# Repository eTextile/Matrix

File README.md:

# E256 - eTextile matrix sensor
### Transforming textiles into an intuitive way to interact with computers
This project is still in a beta phase, where drastic changes may occur and backwards compatibility is not guaranteed until the final release.

## About The project
Using a fabric to sense the touch is now possible with the E256 - eTextile matrix sensor.
The E256 development kit is a highly customizable solution for designers, makers, and companies who want to combine textile and programming into new eTextile projects.
This kit features 30cm by 30cm sensitive textile that allows multi-touch sensing and pressures topographic analysis.
Made out of conductive textile shaped in rows and columns and a layer of piezoresistive fabric, this textile sensor is designed to be easy to make.
The E256 firmware implements all the functionalities to sense the touch and trigger OSC messages that can be used in many application such as PureData, SuperCollider, etc.
The E256 firmware is running on Teensy 3.1 & 3.2 MCUs.
The electronic hardware and the firmware are free and open source and can be easily ported to others Arduino like microcontrollers.
In order to use the sensor in combination with any mobile devices, the E256 firmware will be ported on MCU with BLE capabilities.
From the beginning, this project stimulates the development of technologies in artistic use cases: playing music, combine graphics and sound, imagine objects that can have tactile properties, etc.

### Development tools & DOCs
* **Web page:** [http://matrix.eTextile.org/](http://matrix.eTextile.org "Web page")
* **Repository:** [https://github.com/eTextile/Matrix/tree/master](https://github.com/eTextile/Matrix/tree/master "Project repository")
* **License:** [CC-BY-SA](https://github.com/eTextile/Matrix/tree/Blob/LICENSE "E256 Matrix license")
* **Mail:** [matrix@etextile.org](mailto:contact@etextile.org "eMail")
* **Pictures:** [flickr.com](https://www.flickr.com/photos/maurin/albums/72157673740361510/ "Share your pictures with us")

## Project content
* **Hardware_textile:** eTextile matrix sensor tutorial
* **Hardware_electronic:** extension board PCB sources
* **Firmware:** embedded blob detection with OSC communication
* **Softwear:** demos made with cool applications

## Publications
- [NIME17](http://www.nime2017.org/) - Designing a Multi-Touch eTextile for Music Performances / [Paper](https://github.com/eTextile/Matrix/blob/teensy_matrix/docs/publications/NIME17-eTextile.pdf) - [Video](https://vimeo.com/217690743)
- [MOCO17](http://moco17.movementcomputing.org/) - Music Skin: Fabric Interface for Expressive Music Control / [Paper](https://github.com/eTextile/Matrix/blob/teensy_matrix/docs/publications/MOCO17-MusicSkin.pdf)

## Copyright
Except as otherwise noted, all files in the **E256 eTextile-matrix-sensor** project folder

    Copyright (c) 2014-2020 Maurin Donneaud

For information on usage and redistribution, and for a DISCLAIMER OF ALL
WARRANTIES, see LICENSE.txt included in the resistiveMatrix project folder.

## Acknowledgements
Thanks to Vincent Roudaut, Hannah Perner Willson, Cedric Honnet, Antoine Meisso, Paul Strohmeier

## Docs
- [Video made at Schmiede 2014](http://www.kobakant.at/DIY/?p=4305/)

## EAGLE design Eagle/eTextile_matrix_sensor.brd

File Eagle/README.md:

# e-Textile matrix sensor

- Purpose : 16x16 e-textile matrix sensors
- Copyright (c) 2014 Maurin Donneaud
- Licence : GNU GENERAL PUBLIC LICENSE
- Web site : http://etextile.org

## Partslist

| Part        |    Value                     |     Device              |          Package     |
|-------------|:-----------------------------|:------------------------|:---------------------|
ANALOG_INPUT  | 3.3V                         | PINHD-1X16/90           | 1X16/90              |
ANALOG_INPUT1 | 3.3V                         | PINHD-1X16              | 1X16                 |
C1            | 4.7uF                        | CAP0805                 | 0805                 |
C2            | 4.7uF                        | CAP0805                 | 0805                 |
C3            | 10uf                         | CPOL-EUE1.8-4           | E1,8-4               |
D1            | RED                          | LED1206                 | LED-1206             |
D11           | RED                          | LED1206                 | LED-1206             |
DIGITAL_OUT   |                              | PINHD-1X16/90           | 1X16/90              |
DIGITAL_OUT1  | 3.3V                         | PINHD-1X16/90           | 1X16/90              |
JP7           | LiPo Battery                 | M02-JST-2MM-SMT         | JST-2-SMD            |
R1            | 2K                           | RESISTOR0805-RES        | 0805                 |
R2            | 330                          | RESISTOR0805-RES        | 0805                 |
R3            | 330                          | RESISTOR0805-RES        | 0805                 |
RN1           | 3.3V                         | G08R                    | SIL9                 |
RN2           | 3.3V                         | G08R                    | SIL9                 |
S1            | SWITCH                       | SWITCH-SPSTSMD          | AYZ0202              |
SWITCH1       | SWITCH-MOMENTARY-2           | SWITCH-MOMENTARY-2      | TACTILE_SWITCH_TALL  |
U$1           | TEENSY_3.1_ALL_PINS_AND_PADS | TEENSY_3.1_ALL_PINS_AND_PADS | TEENSY_3.1_ALLPINS   |
U1            | MCP73831                     | MCP73831                     | SOT23-5              |
U3            |                              | AUDIO-JACKSMD2               | AUDIO-JACK-3.5MM-SMD |

## TODO
- Replace the Teensy With an other chip
  - keep compatibility with the Teensy audo lib : http://www.pjrc.com/teensy/td_libs_Audio.html
- Make the design with Upverter

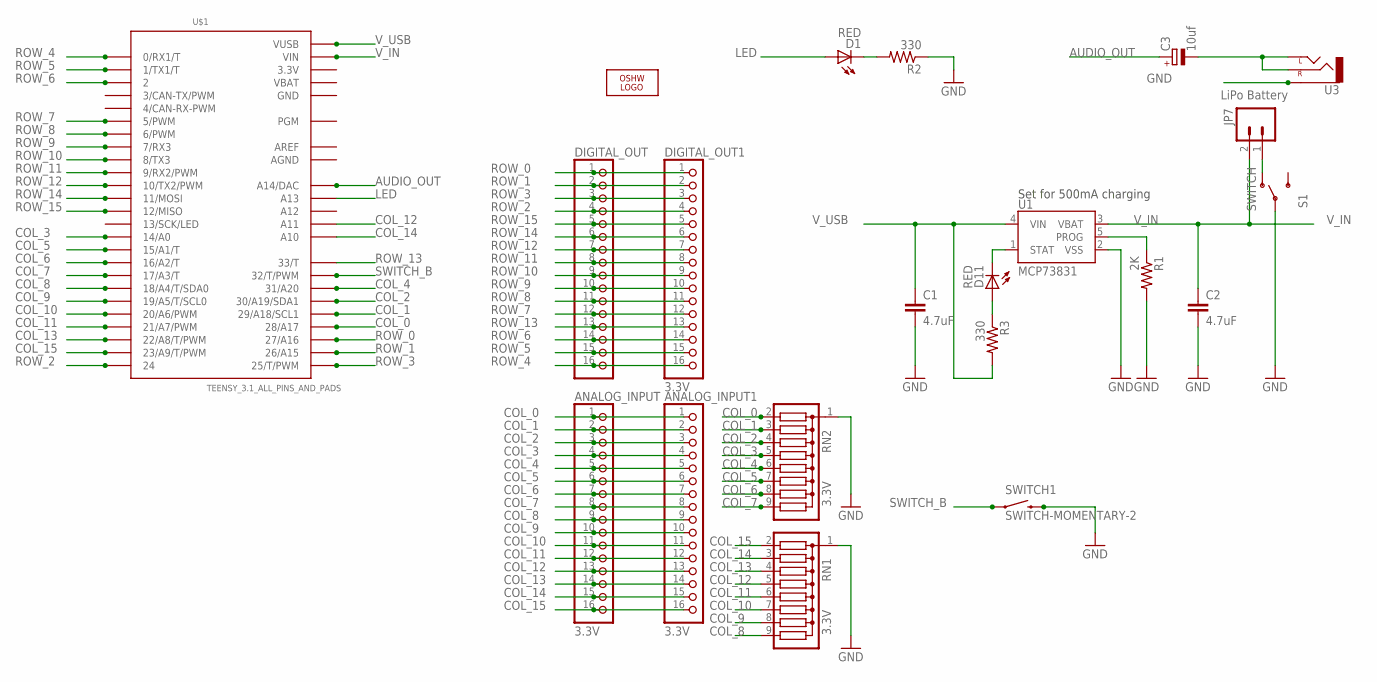
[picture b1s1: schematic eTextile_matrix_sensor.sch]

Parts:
ANALOG_INPUT: 3.3V; 1X16/90
ANALOG_INPUT1: 3.3V; 1X16
C1, C2: 4.7uF; 0805
C3: 10uf; E1,8-4
D1, D11: RED; LED-1206
DIGITAL_OUT: PINHD-1X16/90; 1X16/90
DIGITAL_OUT1: 3.3V; 1X16/90
JP7: LiPo Battery; JST-2-SMD
LOGO1: OSHW_LOGO_8MILX0350-NT; OSHW_8X350_NOTEXT
R1: 2K; 0805
R2, R3: 330; 0805
RN1, RN2: 3.3V; SIL9
S1: SWITCH; AYZ0202
SWITCH1: SWITCH-MOMENTARY-2; TACTILE_SWITCH_TALL
U1: MCP73831; SOT23-5
U3: AUDIO-JACKSMD2; AUDIO-JACK-3.5MM-SMD
U$1: TEENSY_3.1_ALL_PINS_AND_PADS; TEENSY_3.1_ALLPINS

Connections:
3.3V: U$1.3.3V, U$1.3.3V1 (3.3V), U$1.3.3V2 (3.3V)
AGND: U$1.AGND
AREF: U$1.AREF
AUDIO_OUT: C3.+, U$1.A14 (A14/DAC)
COL_0: ANALOG_INPUT.1, ANALOG_INPUT1.1, RN2.2, U$1.28 (28/A17)
COL_1: ANALOG_INPUT.2, ANALOG_INPUT1.2, RN2.3, U$1.29 (29/A18/SCL1)
COL_2: ANALOG_INPUT.3, ANALOG_INPUT1.3, RN2.4, U$1.30 (30/A19/SDA1)
COL_3: ANALOG_INPUT.4, ANALOG_INPUT1.4, RN2.5, U$1.14/A0
COL_4: ANALOG_INPUT.5, ANALOG_INPUT1.5, RN2.6, U$1.31 (31/A20)
COL_5: ANALOG_INPUT.6, ANALOG_INPUT1.6, RN2.7, U$1.15/A1 (15/A1/T)
COL_6: ANALOG_INPUT.7, ANALOG_INPUT1.7, RN2.8, U$1.16/A2 (16/A2/T)
COL_7: ANALOG_INPUT.8, ANALOG_INPUT1.8, RN2.9, U$1.17/A3 (17/A3/T)
COL_8: ANALOG_INPUT.9, ANALOG_INPUT1.9, RN1.9, U$1.18/A4 (18/A4/T/SDA0)
COL_9: ANALOG_INPUT.10, ANALOG_INPUT1.10, RN1.8, U$1.19/A5 (19/A5/T/SCL0)
COL_10: ANALOG_INPUT.11, ANALOG_INPUT1.11, RN1.7, U$1.20/A6 (20/A6/PWM)
COL_11: ANALOG_INPUT.12, ANALOG_INPUT1.12, RN1.6, U$1.21/A7 (21/A7/PWM)
COL_12: ANALOG_INPUT.13, ANALOG_INPUT1.13, RN1.5, U$1.A11
COL_13: ANALOG_INPUT.14, ANALOG_INPUT1.14, RN1.4, U$1.22/A8 (22/A8/T/PWM)
COL_14: ANALOG_INPUT.15, ANALOG_INPUT1.15, RN1.3, U$1.A10
COL_15: ANALOG_INPUT.16, ANALOG_INPUT1.16, RN1.2, U$1.23/A9 (23/A9/T/PWM)
GND: C1.2, C2.2, R1.2, R2.1, RN1.1, RN2.1, S1.2, SWITCH1.B2 (2), U1.2 (VSS), U3.SLEEVE, U$1.GND, U$1.GND1 (GND), U$1.GND2 (GND)
LED: D1.A, U$1.A13
unnamed: C3.-, U3.RING (RIGHT), U3.TIP (LEFT)
unnamed: D11.A, R3.1
unnamed: JP7.1, S1.1 (O)
unnamed: D1.C, R2.2
PROG: R1.1, U1.5 (PROG)
ROW_0: DIGITAL_OUT.1, DIGITAL_OUT1.1, U$1.27 (27/A16)
ROW_1: DIGITAL_OUT.2, DIGITAL_OUT1.2, U$1.26 (26/A15)
ROW_2: DIGITAL_OUT.4, DIGITAL_OUT1.4, U$1.24
ROW_3: DIGITAL_OUT.3, DIGITAL_OUT1.3, U$1.25 (25/T/PWM)
ROW_4: DIGITAL_OUT.16, DIGITAL_OUT1.16, U$1.0 (0/RX1/T)
ROW_5: DIGITAL_OUT.15, DIGITAL_OUT1.15, U$1.1 (1/TX1/T)
ROW_6: DIGITAL_OUT.14, DIGITAL_OUT1.14, U$1.2
ROW_7: DIGITAL_OUT.12, DIGITAL_OUT1.12, U$1.5 (5/PWM)
ROW_8: DIGITAL_OUT.11, DIGITAL_OUT1.11, U$1.6 (6/PWM)
ROW_9: DIGITAL_OUT.10, DIGITAL_OUT1.10, U$1.7 (7/RX3)
ROW_10: DIGITAL_OUT.9, DIGITAL_OUT1.9, U$1.8 (8/TX3)
ROW_11: DIGITAL_OUT.8, DIGITAL_OUT1.8, U$1.9 (9/RX2/PWM)
ROW_12: DIGITAL_OUT.7, DIGITAL_OUT1.7, U$1.10 (10/TX2/PWM)
ROW_13: DIGITAL_OUT.13, DIGITAL_OUT1.13, U$1.33 (33/T)
ROW_14: DIGITAL_OUT.6, DIGITAL_OUT1.6, U$1.11 (11/MOSI)
ROW_15: DIGITAL_OUT.5, DIGITAL_OUT1.5, U$1.12 (12/MISO)
STAT: D11.C, U1.1 (STAT)
SWITCH_B: SWITCH1.A2 (1), U$1.32 (32/T/PWM)
VBAT: U$1.VBAT
V_IN: C2.1, JP7.2, U1.3 (VBAT), U$1.VIN
V_USB: C1.1, R3.2, U1.4 (VIN), U$1.VUSB

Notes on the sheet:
Set for 500mA charging

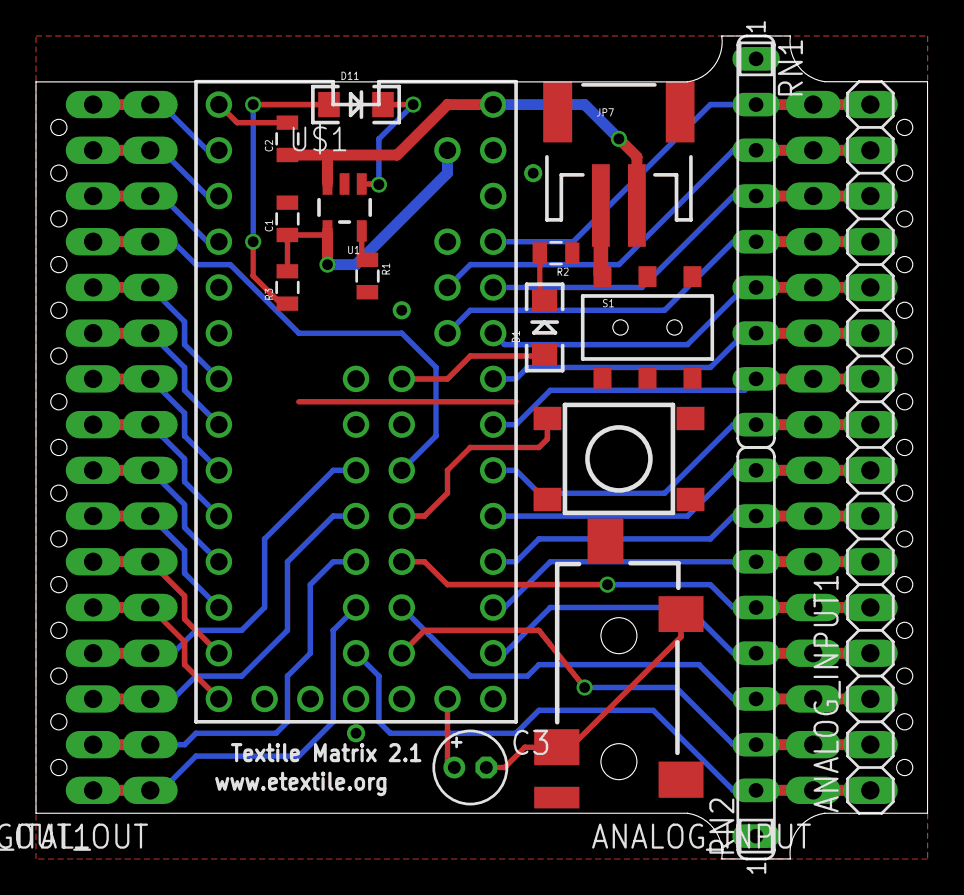
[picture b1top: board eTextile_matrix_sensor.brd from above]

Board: 2 copper layers, 49.5 x 45.7 mm, 21 parts (0 on the bottom side), 45 nets.

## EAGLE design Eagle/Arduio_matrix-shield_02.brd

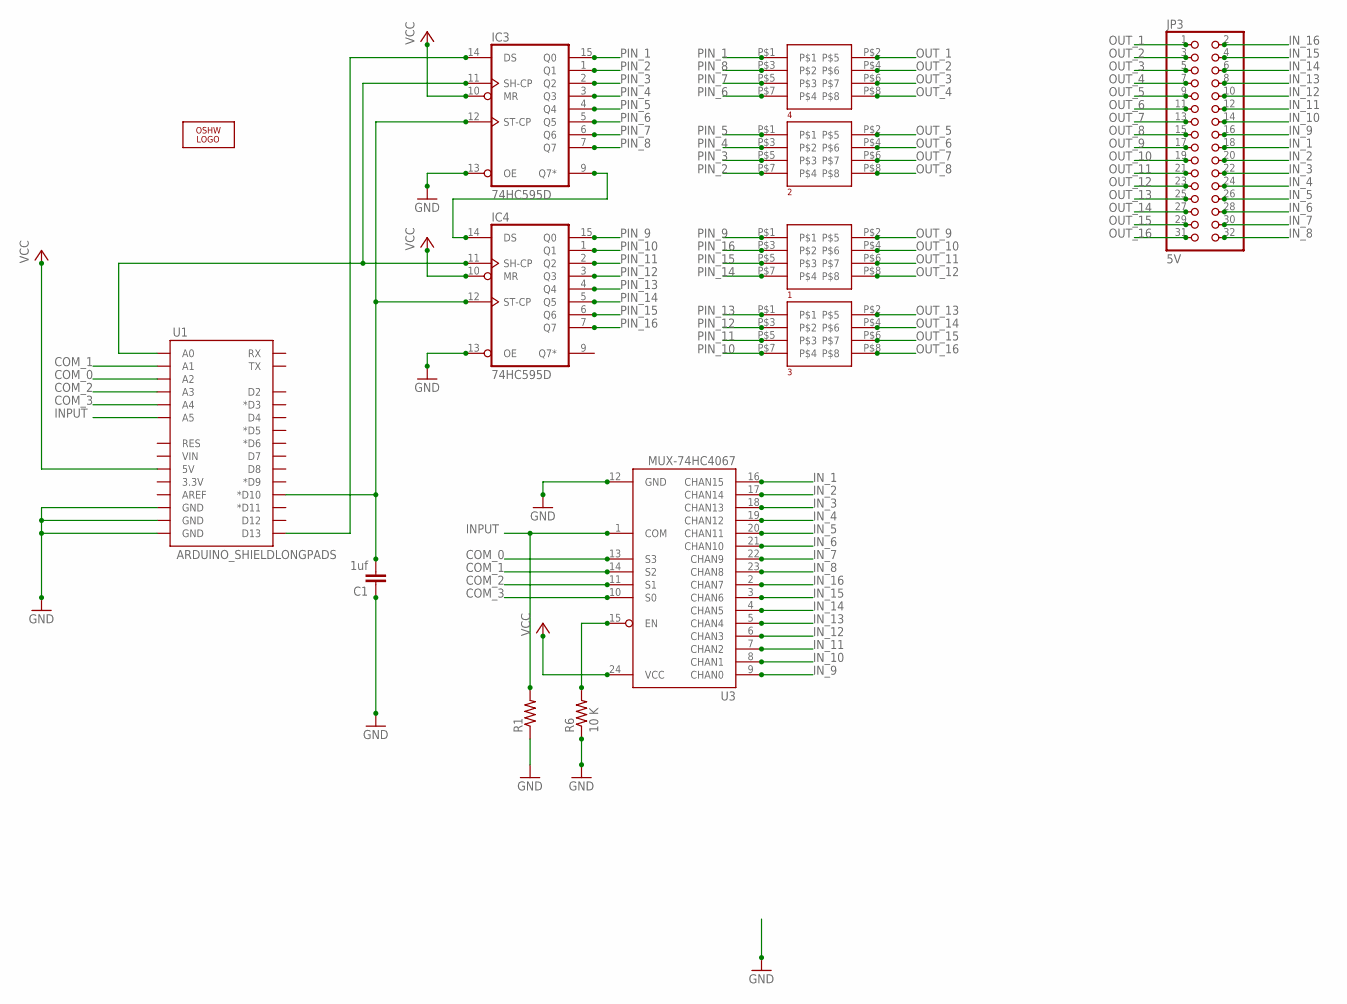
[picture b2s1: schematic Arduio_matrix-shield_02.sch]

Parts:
1, 2, 3, 4: D83A
C1: 1uf; 1206
IC3, IC4: 74HC595D; SO16
JP3: 5V; 2X16/90
OSHW: OSHW_LOGO_8MILX0350-NT; OSHW_8X350_NOTEXT
R1: R-US_0204/7; 0204/7
R6: 10 K; 1206
U1: ARDUINO_SHIELDLONGPADS; DUEMILANOVE_SHIELD_LONGPADS
U3: MUX-74HC4067; SSOP24

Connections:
COM_0: U1.A2, U3.13 (S3)
COM_1: U1.A1, U3.14 (S2)
COM_2: U1.A3, U3.11 (S1)
COM_3: U1.A4, U3.10 (S0)
GND: C1.1, IC3.8 (GND), IC3.13 (OE), IC4.8 (GND), IC4.13 (OE), R1.1, R6.1, U1.GND@0 (GND), U1.GND@1 (GND), U1.GND@2 (GND), U3.12 (GND)
INPUT: R1.2, U1.A5, U3.1 (COM)
IN_1: JP3.18, U3.16 (CHAN15)
IN_2: JP3.20, U3.17 (CHAN14)
IN_3: JP3.22, U3.18 (CHAN13)
IN_4: JP3.24, U3.19 (CHAN12)
IN_5: JP3.26, U3.20 (CHAN11)
IN_6: JP3.28, U3.21 (CHAN10)
IN_7: JP3.30, U3.22 (CHAN9)
IN_8: JP3.32, U3.23 (CHAN8)
IN_9: JP3.16, U3.9 (CHAN0)
IN_10: JP3.14, U3.8 (CHAN1)
IN_11: JP3.12, U3.7 (CHAN2)
IN_12: JP3.10, U3.6 (CHAN3)
IN_13: JP3.8, U3.5 (CHAN4)
IN_14: JP3.6, U3.4 (CHAN5)
IN_15: JP3.4, U3.3 (CHAN6)
IN_16: JP3.2, U3.2 (CHAN7)
unnamed: IC3.9 (Q7*), IC4.14 (DS)
unnamed: R6.2, U3.15 (EN)
unnamed: IC3.11 (SH-CP), IC4.11 (SH-CP), U1.A0
unnamed: C1.2, IC3.12 (ST-CP), IC4.12 (ST-CP), U1.D10 (*D10)
unnamed: IC3.14 (DS), U1.D13
OUT_1: 4.P$2, JP3.1
OUT_2: 4.P$4, JP3.3
OUT_3: 4.P$6, JP3.5
OUT_4: 4.P$8, JP3.7
OUT_5: 2.P$2, JP3.9
OUT_6: 2.P$4, JP3.11
OUT_7: 2.P$6, JP3.13
OUT_8: 2.P$8, JP3.15
OUT_9: 1.P$2, JP3.17
OUT_10: 1.P$4, JP3.19
OUT_11: 1.P$6, JP3.21
OUT_12: 1.P$8, JP3.23
OUT_13: 3.P$2, JP3.25
OUT_14: 3.P$4, JP3.27
OUT_15: 3.P$6, JP3.29
OUT_16: 3.P$8, JP3.31
PIN_1: 4.P$1, IC3.15 (Q0)
PIN_2: 2.P$7, IC3.1 (Q1)
PIN_3: 2.P$5, IC3.2 (Q2)
PIN_4: 2.P$3, IC3.3 (Q3)
PIN_5: 2.P$1, IC3.4 (Q4)
PIN_6: 4.P$7, IC3.5 (Q5)
PIN_7: 4.P$5, IC3.6 (Q6)
PIN_8: 4.P$3, IC3.7 (Q7)
PIN_9: 1.P$1, IC4.15 (Q0)
PIN_10: 3.P$7, IC4.1 (Q1)
PIN_11: 3.P$5, IC4.2 (Q2)
PIN_12: 3.P$3, IC4.3 (Q3)
PIN_13: 3.P$1, IC4.4 (Q4)
PIN_14: 1.P$7, IC4.5 (Q5)
PIN_15: 1.P$5, IC4.6 (Q6)
PIN_16: 1.P$3, IC4.7 (Q7)
VCC: IC3.10 (MR), IC3.16 (VCC), IC4.10 (MR), IC4.16 (VCC), U1.5V, U3.24 (VCC)

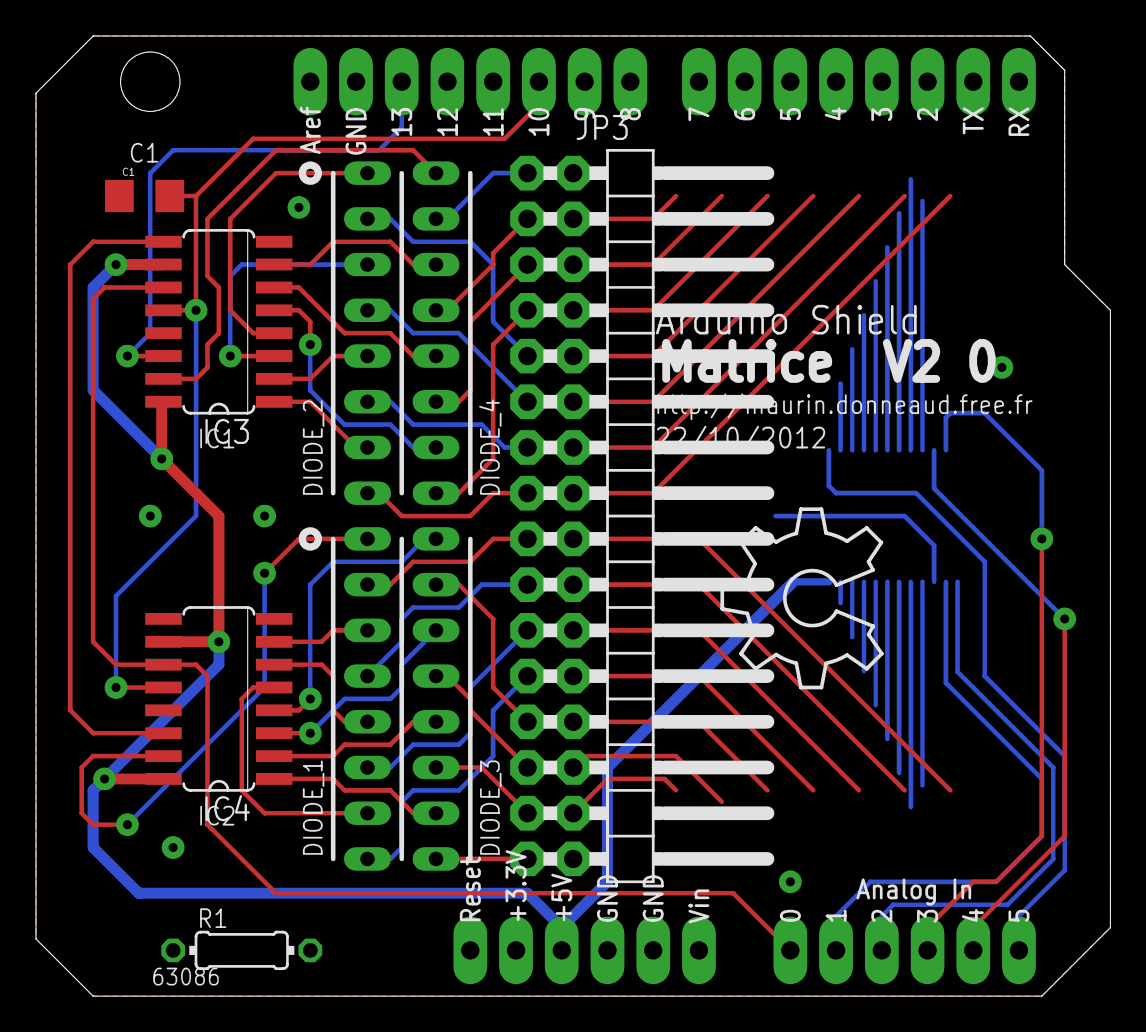
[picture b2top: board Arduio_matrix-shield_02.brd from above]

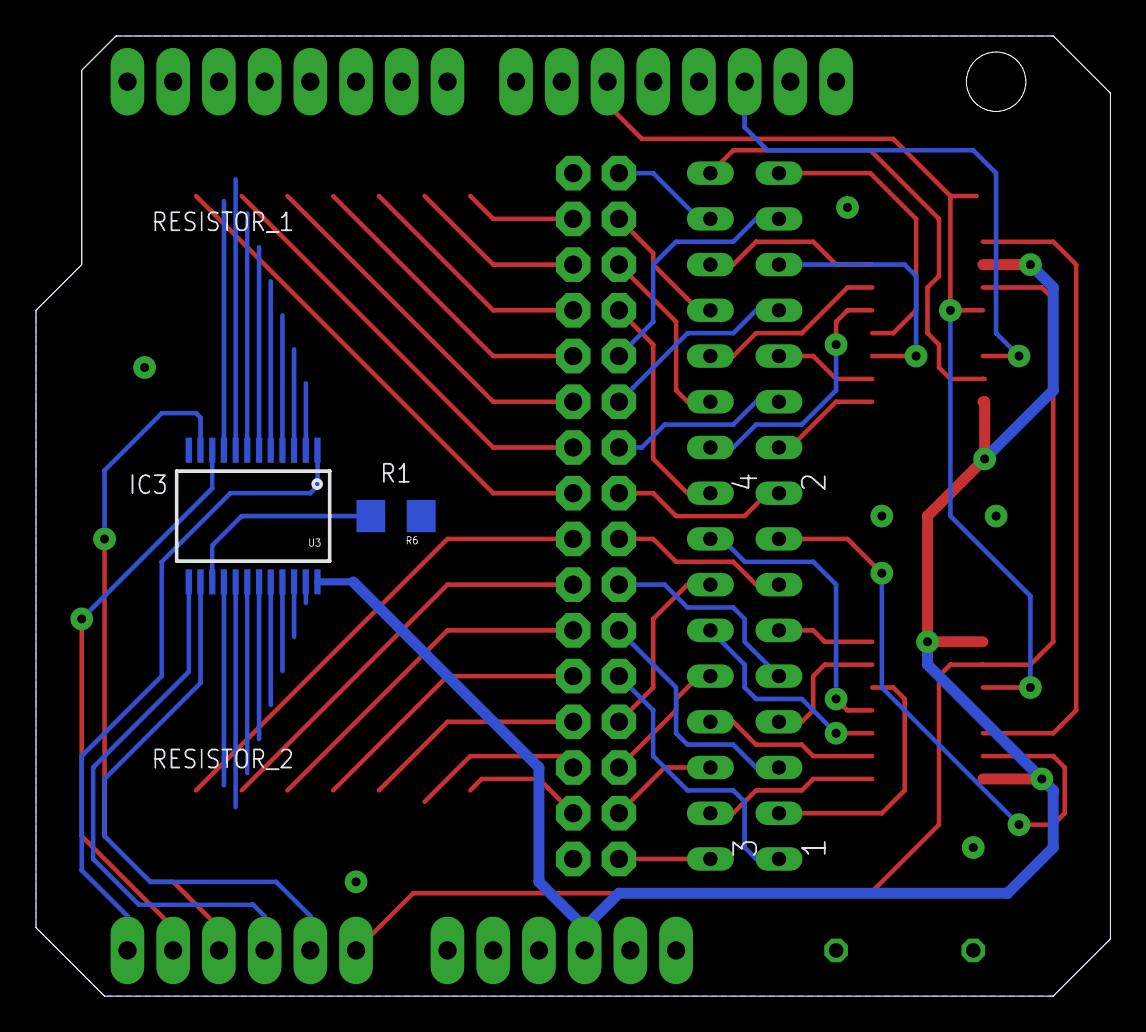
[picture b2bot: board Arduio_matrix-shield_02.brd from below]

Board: 2 copper layers, 59.7 x 53.3 mm, 13 parts (6 on the bottom side), 60 nets.

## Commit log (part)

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2016-10-31 Clean : aesthetics, wrong link...
2016-10-31 New : OSC input for debug use without Arduino device
2016-10-31 New : /reset message
2016-10-31 New : a bit more documentation
2016-11-01 Added corrections
2016-11-01 little text correction
2016-11-02 Added window title
2016-11-02 Clean up
2016-11-30 New : persistant blob ID
2016-12-14 Fix : Project config for makefiles
2016-12-14 Fix addons.make.
2016-12-14 Accelerate compilation using ccache.
2017-01-03 Added TODO list
2017-01-03 Fix include missing.
2017-01-10 Toggle full screen when pressing 'f'.
2017-01-28 Update URLs with new repo, and add contributors.
2017-01-28 Set theme jekyll-theme-architect
2017-05-01 Add NIME17 + MOCO17 publications.
2017-05-22 Added CC-BY-SA license
2017-05-22 Updated license
2017-05-26 NIME demo: Not full screen by default - shrink a bit.
2017-06-21 added BUGFIX solution
2017-06-21 new electronic PCB
2017-06-21 Added the E256 Arduino driver
2017-06-23 Updated calibration fonction & clean up
2017-07-04 Updated OSC remove unused variables
2017-07-04 Updated README/TODO
2017-07-07 Added pictures
2017-07-07 added .svg for printing
2017-07-07 Readme corrections
2017-08-24 Added Arduino CMSIS bilinear interpolation example
2017-08-24 Updated Sketch
2017-08-24 FIX the bilinear interpolation example
2017-08-24 Added bilinear interpolation
2017-08-24 Added bloc tracking from OpenMV
2017-08-25 Added new PCB picture
2017-08-26 Added fb_alloc.c & .h
2017-08-28 Renamed imlib.h to blob.h
2017-08-28 FIX #include
2017-08-28 Update for the Teensy Prototype version
2017-08-28 Remove unneeded files
2017-08-28 Renamed files
2017-09-06 Updating calibration()
2017-09-06 Updated calibration()
2017-09-06 Still BUGED
2017-09-13 trying to get rid of micropython in order to compile the blob tracking with arduino IDE. How can i replace the memory allocation functions py/gc.c used in the code.
2017-09-16 traying to remove maloc
2017-09-19 Added framebuffer.c framebuffer.h
2017-09-20 Added some explanations & renamed variables
2017-09-25 Updated calibrate() & renamed fonctions
2017-09-26 Added heap allocator files
2017-09-27 playing with bilinear interpolation ;-)
2017-09-28 Tryng to fix #includes
2017-09-30 Added Makfile
2017-10-02 Added gitignore for build-teensy & build-uno
2017-10-02 supress .c fils
2017-10-03 ERROR: FB Alloc Collision!
2017-10-03 Removed fb_alloc_fail()
2017-10-03 Makefile should be cross platform now
2017-10-03 added makefile folder
2017-10-13 removal of dynamic allocation
2017-10-13 Added FPS
2017-10-13 blob
2017-10-17 list_pop_front() dont work!?
2017-10-18 WORKING but still some Bugs!!!!!!!
2017-10-23 added DEBUG & config.h
2017-10-26 The nodes and pointers makes holes in my brain
2017-10-27 NEW list_copy() with home made garbage collector!
2017-11-05 Work is progress
2017-11-08 minor changes
2017-11-08 remove unused linked list
2017-11-15 the bug start to be quit
2017-12-09 Updated list_copy() THX Drix!
2017-12-20 C'est pas facile mais Ca fait du bien
2017-12-22 Added work attribution
2017-12-23 Updated list_remove_blob()
2018-01-11 Updated lifo_alloc_all()
2018-01-16 Updated lifo
2018-02-24 Updated webpage
2018-02-24 Updated web mail
2018-02-27 ADC input is now set to 8-bit
2018-02-27 Still trying to fix the blob tracking
2018-02-28 the medium is the message
2018-02-28 Fix some bugs in the Lifo
2018-02-28 still some Blobs lost in translation
2018-03-01 temporary commit for a perverse blob
2018-03-01 Minor Swing
2018-03-02 Lifo is not working properly
2018-03-05 Get rid of the lifo mencopy
2018-03-09 Added new ADC lib
2018-03-09 CleanUP
2018-03-14 Spelling
2018-03-14 Small update
2018-03-15 Moved collections to blob.cpp
2018-03-15 Added new blob.h file
2018-03-15 Updated firmware & removed Lifo fonctions
2018-03-15 Removed fmath.cpp & fmath.h
2018-03-15 Renamed MAIN
2018-03-16 Added folder to put eTextile pattern
2018-03-18 Added HOWTO eTextile hardware
2018-03-18 Added Dual synchronized ADC
2018-03-18 Minor change
2018-03-18 Added PureData OSC driver
2018-03-18 Added DEBUG OSC/SERIAL
2018-03-19 Merging attempt (with all the mess)
2018-03-19 oups
2018-03-19 not WORKING yet
2018-03-22 Added new picture & updated text
2018-03-22 Added InCut Github link
2018-03-23 Added Firmware folder
2018-03-23 reorganized files & ADC BUGFIX attempt
2018-03-23 ALL IS WORKING
2018-03-24 Updated picture
2018-03-24 Added E256 LOGO
2018-03-24 Updated LOGO
2018-03-24 Added ARTE video link
2018-03-24 Smal update
2018-03-24 Moved CNAME to /docs
2018-03-24 Updated title
2018-03-24 Updated CSS link
2018-03-26 New webpage
2018-03-26 Removed webpage README
2018-03-26 Added TODO & updated hardware routing mapping
2018-03-26 OSC BUGFIX - Added msg.empty()
2018-03-27 Added Pure Data OSC driver
2018-03-28 Updated form
2018-04-01 syntax errors
2018-04-01 Added E256_path.svg
2018-04-02 Updated paper weblinks
2018-04-02 Added state_t for blob state
2018-04-10 Added custom interpolation
2018-04-10 Removed branches to make the REDME more standard
2018-04-11 Updated branches weblink
2018-04-12 Interpolation optimization attempt with static method
2018-04-17 Updated the new 2D linear interpolation but still nead some work
2018-04-17 Updated 2D linear interpolation : FIXME: outIndex computation
2018-04-17 Updated interpolation stand alone
2018-04-17 Working 2D interpolation
2018-04-17 Renamed variables
2018-04-17 Bilinear inerp small fix
2018-04-18 Updated new path
2018-04-18 #include FIXME
2018-04-18 WIP: bugs fixes: now compiles.
2018-04-23 Added SLIP-OSC comumnication
2018-04-30 Updated SLIP-OSC
2018-04-30 Added beta phase warning sentence
2018-05-18 merged file with the MASTER.pd
2018-05-18 Breaked
2018-05-18 attempt to add SLIP in SC
2018-09-19 Clean markdownDD
2018-09-19 Added SOFTWARE_README
2018-09-19 Clean Markdown
2018-11-22 Removing blob tracking of the host application - this is done by the embedded firmware
2018-11-27 Removed XCode config files
2018-11-27 Updated openFrameworks driver for SLIP-OSC communication
2018-12-15 Added new SLIP-OSC communication with Firmware
2018-12-15 testing SLIP-OSC parcing
2018-12-15 Updated SLIP-OSC for blobs communication
2019-01-14 added new blob description and communication : (UID, centroid.X, centroid.Y, rect.W, rect.H, rect.Z);
2019-01-14 Updatad for new blob definition
2019-01-14 Updatad README
2019-01-14 Updatad new blobs spécifications & communication
2019-01-14 Updatad blob struct (rect -> box)
2019-04-21 Major update / updated SLIP-OSC packet
2019-04-21 New driver
2019-04-21 New SLIP-OSC serial driver
2019-04-21 Formatted
2019-04-24 Added linked list bubbleSort()
2019-05-04 llist_sort updated
2019-05-07 Improved llist
2019-05-07 Added new alive OSC uint8_t paket
2019-05-10 Changed pilot software request OSC messages & clean up
2019-05-10 Added OSC communication specs & filers
2019-05-10 Added Processing SLIP-OSC sketch (in progress)
2019-05-16 Cleaned all DEBUGS
2019-05-21 BUGFIX with Z bolobs value
2019-05-21 FIXME
2019-05-27 Added raw frame 3D
2019-05-30 Added some optim & InterpolatedFrame transmition
2019-05-30 Added InterpolatedFrame request
2019-05-30 Added new communication specs & Alive status
2019-06-24 Added lifo
2019-06-24 New blob detection from OpenMV ;-)
2019-06-24 Updated config file
2019-06-24 Moved main.h into MAIN.ino
2019-06-24 Removed double declaration
2019-06-25 Improved sqrt() and blobs size computation
2019-07-24 Added libpd patch
2019-07-24 Add all libPd project
2019-09-09 Added polar mapping
2019-09-09 Added record score Flavin Berger
2019-09-15 renaming
2019-09-15 added libPd path
2019-09-25 Added Bela driver
2019-09-25 Bump handlebars from 4.0.12 to 4.3.1 in /docs
    Bumps [handlebars](https://github.com/wycats/handlebars.js) from 4.0.12 to 4.3.1.
    - [Release notes](https://github.com/wycats/handlebars.js/releases)
    - [Changelog](https://github.com/wycats/handlebars.js/blob/v4.3.1/release-notes.md)
    - [Commits](https://github.com/wycats/handlebars.js/compare/v4.0.12...v4.3.1)
2019-09-25 Bump mixin-deep from 1.3.1 to 1.3.2 in /docs
    Bumps [mixin-deep](https://github.com/jonschlinkert/mixin-deep) from 1.3.1 to 1.3.2.
    - [Release notes](https://github.com/jonschlinkert/mixin-deep/releases)
    - [Commits](https://github.com/jonschlinkert/mixin-deep/compare/1.3.1...1.3.2)
2019-09-25 Bump js-yaml from 3.12.1 to 3.13.1 in /docs
    Bumps [js-yaml](https://github.com/nodeca/js-yaml) from 3.12.1 to 3.13.1.
    - [Release notes](https://github.com/nodeca/js-yaml/releases)
    - [Changelog](https://github.com/nodeca/js-yaml/blob/master/CHANGELOG.md)
    - [Commits](https://github.com/nodeca/js-yaml/compare/3.12.1...3.13.1)
2019-10-09 will be update soon
2019-10-09 Added Rasberry_pi project
2019-10-09 Updated Pd paches
2019-10-09 BUGFIX :-)
2019-10-09 Added info to load added libs into Pd
2019-10-09 Added controls
2019-10-09 TOFIX for Bela
2019-10-09 Removed Bela I/O pins
2019-11-04 sound-card & autostart
2019-11-14 Added new slogan
2019-11-14 Updated typo
2019-11-14 added address
2019-11-14 Added favicon
2019-11-17 Typo updates
2019-11-17 Update typos
2019-11-18 Added Publication
2019-11-19 Bump tar from 2.2.1 to 2.2.2 in /docs
    Bumps [tar](https://github.com/npm/node-tar) from 2.2.1 to 2.2.2.
    - [Release notes](https://github.com/npm/node-tar/releases)
    - [Commits](https://github.com/npm/node-tar/compare/v2.2.1...v2.2.2)
2019-11-19 Bump lodash.mergewith from 4.6.1 to 4.6.2 in /docs
    Bumps [lodash.mergewith](https://github.com/lodash/lodash) from 4.6.1 to 4.6.2.
    - [Release notes](https://github.com/lodash/lodash/releases)
    - [Commits](https://github.com/lodash/lodash/commits)
2019-11-19 Bump fstream from 1.0.11 to 1.0.12 in /docs
    Bumps [fstream](https://github.com/npm/fstream) from 1.0.11 to 1.0.12.
    - [Release notes](https://github.com/npm/fstream/releases)
    - [Commits](https://github.com/npm/fstream/compare/v1.0.11...v1.0.12)
2019-11-19 Bump eslint-utils from 1.3.1 to 1.4.3 in /docs
    Bumps [eslint-utils](https://github.com/mysticatea/eslint-utils) from 1.3.1 to 1.4.3.
    - [Release notes](https://github.com/mysticatea/eslint-utils/releases)
    - [Commits](https://github.com/mysticatea/eslint-utils/compare/v1.3.1...v1.4.3)
2019-12-11 Updated weblink and some text
2019-12-11 Added new description
2019-12-11 Web link
2019-12-11 Added doc
2019-12-12 Removed ARTE
2019-12-13 text update
2020-02-20 Added new PCB info
2020-02-20 Kicad in progress
2020-03-14 Bump acorn from 6.0.7 to 6.4.1 in /docs
    Bumps [acorn](https://github.com/acornjs/acorn) from 6.0.7 to 6.4.1.
    - [Release notes](https://github.com/acornjs/acorn/releases)
    - [Commits](https://github.com/acornjs/acorn/compare/6.0.7...6.4.1)
2020-04-25 Added puredata simple SLIP-OSC driver
2020-04-25 Added OSC output
2020-04-25 Fonction renaming
2020-04-28 Include OSC message information in firmware README.md
2020-04-29 Bump jquery from 3.4.0 to 3.5.0 in /docs
    Bumps [jquery](https://github.com/jquery/jquery) from 3.4.0 to 3.5.0.
    - [Release notes](https://github.com/jquery/jquery/releases)
    - [Commits](https://github.com/jquery/jquery/compare/3.4.0...3.5.0)
2020-04-30 Added threshold substraction
2020-09-04 Bump node-sass from 4.11.0 to 4.13.1 in /docs
    Bumps [node-sass](https://github.com/sass/node-sass) from 4.11.0 to 4.13.1.
    - [Release notes](https://github.com/sass/node-sass/releases)
    - [Changelog](https://github.com/sass/node-sass/blob/master/CHANGELOG.md)
    - [Commits](https://github.com/sass/node-sass/compare/v4.11.0...v4.13.1)
2020-09-04 Bump handlebars from 4.3.1 to 4.7.6 in /docs
    Bumps [handlebars](https://github.com/wycats/handlebars.js) from 4.3.1 to 4.7.6.
    - [Release notes](https://github.com/wycats/handlebars.js/releases)
    - [Changelog](https://github.com/handlebars-lang/handlebars.js/blob/master/release-notes.md)
    - [Commits](https://github.com/wycats/handlebars.js/compare/v4.3.1...v4.7.6)
2020-09-05 Bump http-proxy from 1.17.0 to 1.18.1 in /docs
    Bumps [http-proxy](https://github.com/http-party/node-http-proxy) from 1.17.0 to 1.18.1.
    - [Release notes](https://github.com/http-party/node-http-proxy/releases)
    - [Changelog](https://github.com/http-party/node-http-proxy/blob/master/CHANGELOG.md)
    - [Commits](https://github.com/http-party/node-http-proxy/compare/1.17.0...1.18.1)
2020-10-09 Removed file
2021-01-05 Updated files
2021-01-09 add space
2021-02-02 Updated board README
2021-06-02 Updated WebPage logo

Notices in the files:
parts and their libraries:
SparkFun-Boards: Licensing: CC v3.0 Share-Alike You are welcome to use this library for commercial purposes.
